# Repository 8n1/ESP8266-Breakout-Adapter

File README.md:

##ESP-07 & ESP-12 Breakout Adapter

###UPDATE [24.03.2016] - All Breakout Adapters are tested and working as expected. 
####Note: Documentations will be updated and completed within the next days.
<br />
####Version 1.1 - LM1117 (tested)
Used LDO: LM1117
Vin=4.8-15V, Dropout=1.2V, Iq=5mA

oshpark: https://oshpark.com/shared_projects/9CsYq2PY

####Version 2.0A - AS1363 (tested)
Used LDO: AS1363
Vin=3.5-5.5V, Dropout=150mV(-320mV), Iq=40µA

oshpark: https://oshpark.com/shared_projects/2IkxaFPm

####Version 2.0B - SPX3819 (tested)
Used LDO: SPX3819 
Vin=3.7-16V, Dropout=340mV(-550mV), Iq=90µA

oshpark: https://oshpark.com/shared_projects/jsl8ZcFp

####Version 3.1A - AS1363 - Mini (tested)
Used LDO: AS1363
Vin=3.5-5.5V, Dropout=150mV(-320mV), Iq=40µA

oshpark: https://oshpark.com/shared_projects/BgaX81QE

####Version 3.1B - SPX3819 - Mini (tested)
Used LDO: SPX3819 
Vin=3.7-16V, Dropout=340mV(-550mV), Iq=90µA

oshpark: https://oshpark.com/shared_projects/zpDg7761

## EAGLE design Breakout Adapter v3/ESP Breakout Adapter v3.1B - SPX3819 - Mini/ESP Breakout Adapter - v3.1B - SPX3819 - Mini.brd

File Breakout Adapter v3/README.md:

## V3 - Mini Adapter

### Changelog/Updates: <br />

V3.1 - Nov, 2015
- Footprint for VREG input and output capacitors changed from 1206 to 0805
- VREG bypass capacitor (C3) removed
- Bigger solderpads for the tactile switches
- Pullup resistor for GPIO2 added (R7)
- Part numbers on bottom side replaced with actual values
- Layout optimized
- Silkscreen fix (description of where the led is connected to was swapped: 3V3<->GPIO13)

V3.0 - Okt, 2015
- First version

### Pictures
V3.1B - OSH Park renderings<br />
&nbsp;

<br />
### Schematic

### Features
* ESP-07, ESP-12, ESP-12E and ESP-12F compatible (bottom header for E and F module is not brought out)
* On-board voltage regulator
* Flash and Reset switch
* Pullup resistors for Reset, CH_PD, GPIO0 and GPIO2
* Pulldown resistor for GPIO15
* On/Off Switch *
* LDO Enable Pin brougth out **
* DeepSleep wake-up jumper - Connects Pin8 and Pin32 and allows automatic deep-sleep wake-up
* On-board LED - Anode(+) can either be connected to the LDO ouptut ("3V3") or to "GPIO13" (selected using solderjumper)
* 2 Mountingholes (2.0mm)*)
* Expect for the headers fully SMD
* Breadboard compatible -> 3 rows stay free
* Very small

\* Can be used to completly shutdown the board and everything connected to it. The current consumption in this state will typically be &lt;1µA.  
\** Can be used to externaly turn the board on if the On/Off switch is set to "Off", or off if the On/Off switch is set to "On".

### Partlist (v3.1)
| Part  | Value                     | Info                |
|:------|:--------------------------|:--------------------|
| IC1   | AS1363-BSTT-33 (SOT23-6)  | Voltage regulator - Variant "A" |
| IC1   | SPX3819M5-L-3-3 (SOT23-5) | Voltage regulator - Variant "B" |
| C1    | 10µF (Ceramic, 0805)      | Input capacitor for the voltage regulator |
| C2    | 10µF (Ceramic, 0805)      | Output capacitor for the voltage regulator |
| C3    | 100nF (Ceramic, 0805)     | Decoupling capacitor for the ESP module |
| R1    | 10K (0805) *              | Pullup resistor for CH_PD |
| R2    | 10K (0805) *              | Pulldown resistor for GPIO15 |
| R3    | 10K (0805)                | Pullup resistor for Reset |
| R4    | 10K (0805)                | Pullup resistor for GPIO0 |
| R7    | 10K (0805)                | Pullup resistor for GPIO2 |
| R5    | 10K (0805)                | Pullup for LDO enable pin |
| R6    | 10K (0805)                | Pulldown for LDO enable pin |
| RV    | ~220 Ohm (0805)           | [Optional] Current limiting resistor for the led ** |
| LED   | LED (0805) **             | [Optional] Led of choice |
| DS    | Solderbridge       | DeepSleep wake-up jumper |
| FLASH | Tactile Pushbutton SMD 2pin 6x3       | Flash button |
| RESET | Tactile Pushbutton SMD 2pin 6x3       | Reset button |
| On/Off | SMD slide switch (DK: CKN10374CT-ND) (<a href="http://www.ebay.at/itm/20PCS-Mini-Slide-Power-Off-On-Panel-PCB-MINI-SMD-Solder-Switch-SPM-/120731615109">ebay</a>)       | On/Off switch |

\* **or** 0Ohm resistor/solderbridge if pin is not needed<br /> 
\** if the led is connected to GPIO13 the led current must be lower then 12mA, calculate the resister value accordingly!

Note:  
Pullup and Pulldown resistors(**R1, R2, R3, R4, R7**)  can range from 4.7K to 10K.  
Pullup and Pulldown resistor for the LDO enable pin(**R5, R6**) should be 10K or higher (100K max).  
Input and output capacitors for the voltage regualtor(**C1, C2**) are LOW ESR ceramic types. (I'm using: SAMSUNG CL21A106KOQNNNG)  

Pinheader
* 2x 1x10 (2.54mm)

Optional "socket" header for the esp module
* 2x 1x8 (2mm) female and male pin header

### Difference between variant A and B
The only difference is the used LDO. Variant A uses the AS1363, variant B the SPX3819(or pincompatible).

#### Resources:
- AS1363 Datasheet - https://ams.com/eng/content/download/1961/15107/file/AS1364_Datasheet_EN_v3.pdf
- SPX3819 Datasheet - https://www.adafruit.com/datasheets/SPX3819_DS_R202_052014.pdf

- More Pictures V3.1 - http://imgur.com/a/jSkG7 (imgur album)
- More Pictures V3.0 - http://imgur.com/a/w46x3 (imgur album)

#### This adapter on OSH Park:
- ESP8266 Breakout v3.1A - https://oshpark.com/shared_projects/RfAN6raq
- ESP8266 Breakout v3.1B - https://oshpark.com/shared_projects/OPku1n9U

#### License
<br />
Creative Commons Attribution 4.0 International<br />
http://creativecommons.org/licenses/by/4.0/

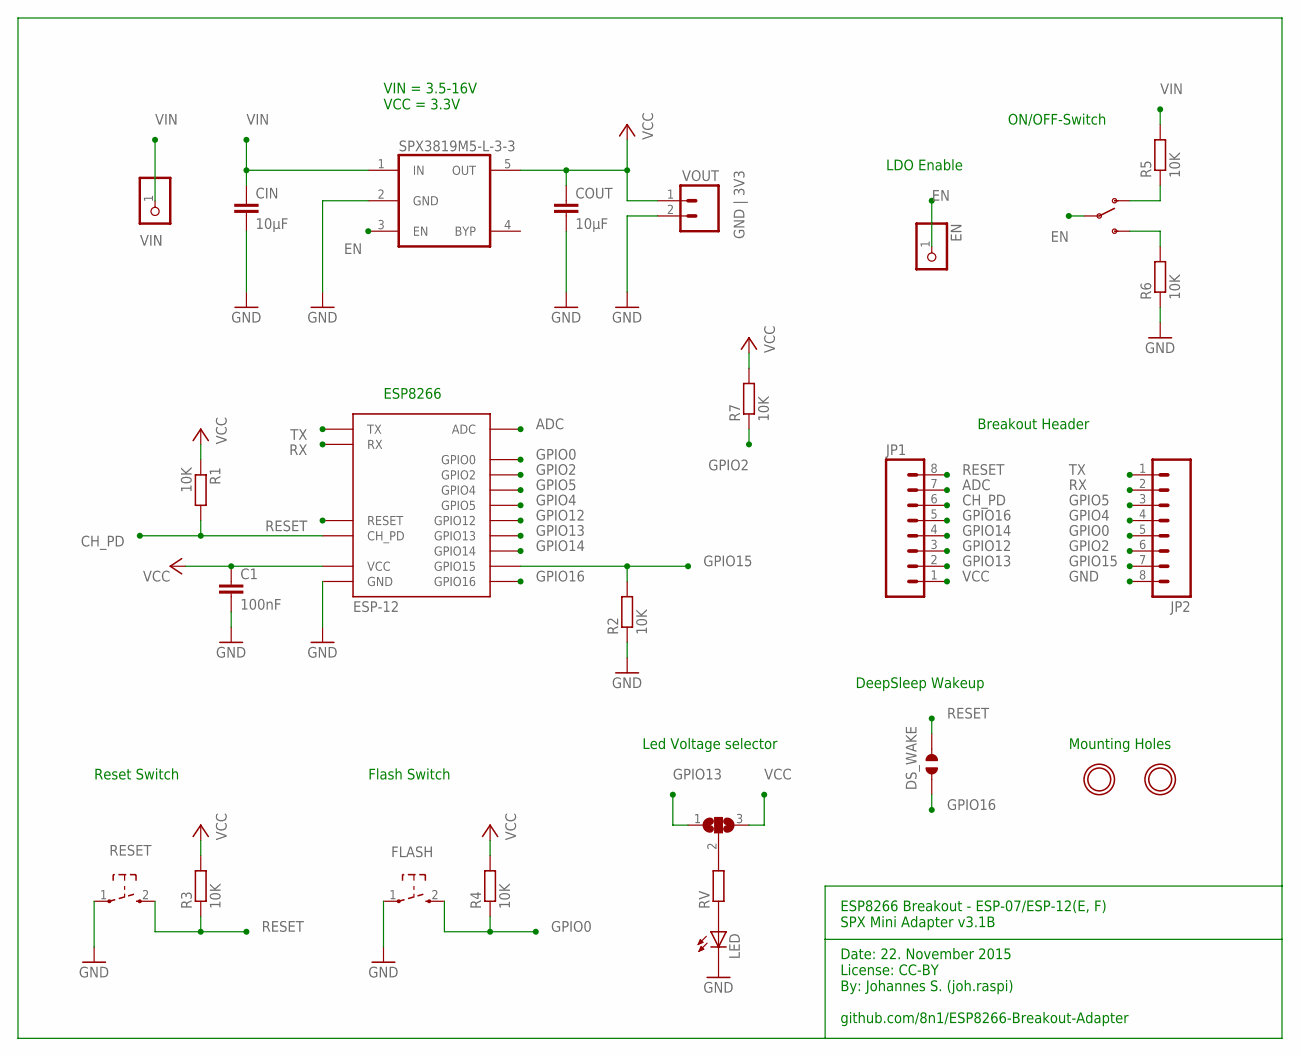
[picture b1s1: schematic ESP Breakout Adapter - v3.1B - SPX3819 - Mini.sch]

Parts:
C1: 100nF; C0805
CIN: 10µF; C0805
COUT: 10µF; C0805
DS_WAKE: JUMPER_SOLDER_1X2
EN: PINHD-1X1; 1X01
FLASH: SW_TACT_2P-3X6; SW_TACT_3X6
JP1, JP2: M081X08; 1X08
LED: LEDCHIPLED_0805; CHIPLED_0805
LED_VOLTAGE: SJ2W; SJ_2
ON/OFF-SWITCH: SWITCH_SPDT; KPS-1290
R1, R2, R3, R4, R5, R6, R7: 10K; R0805
RESET: SW_TACT_2P-3X6; SW_TACT_3X6
RV: R-EU_R0805; R0805
SPX3819M5-L-3-3: VREG_5PINS-SOT-23-5; SOT-23-5
U$1: ESP-12
U$4, U$5: MOUNTINGHOLE2.0; MOUNTINGHOLE_2.0_PLATED
VIN: M01PTH_2MM; 1X01-CLEANBIG
VOUT: GND | 3V3; 1X02

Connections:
123: ON/OFF-SWITCH.S, R6.2
ADC: JP1.7, U$1.ADC
CH_PD: JP1.6, R1.2, U$1.CH_PD
EN: EN.1, ON/OFF-SWITCH.P, SPX3819M5-L-3-3.3 (EN)
GND: C1.2, CIN.2, COUT.2, FLASH.1, JP2.8, LED.C, R2.1, R6.1, RESET.1, SPX3819M5-L-3-3.2 (GND), U$1.GND, VOUT.2
GPIO0: FLASH.2 (3), JP2.5, R4.1, U$1.GPIO0
GPIO2: JP2.6, R7.1, U$1.GPIO2
GPIO4: JP2.4, U$1.GPIO5
GPIO5: JP2.3, U$1.GPIO4
GPIO12: JP1.3, U$1.GPIO12
GPIO13: JP1.2, LED_VOLTAGE.1, U$1.GPIO13
GPIO14: JP1.4, U$1.GPIO14
GPIO15: JP2.7, R2.2, U$1.GPIO15
GPIO16: DS_WAKE.1, JP1.5, U$1.GPIO16
unnamed: LED_VOLTAGE.2, RV.2
unnamed: ON/OFF-SWITCH.O, R5.1
unnamed: LED.A, RV.1
RESET: DS_WAKE.2, JP1.8, R3.1, RESET.2 (3), U$1.RESET
RX: JP2.2, U$1.RX
TX: JP2.1, U$1.TX
VCC: C1.1, COUT.1, JP1.1, LED_VOLTAGE.3, R1.1, R3.2, R4.2, R7.2, SPX3819M5-L-3-3.5 (OUT), U$1.VCC, VOUT.1
VIN: CIN.1, R5.2, SPX3819M5-L-3-3.1 (IN), VIN.1

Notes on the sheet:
ESP8266 Breakout - ESP-07/ESP-12(E, F) SPX Mini Adapter v3.1B Date: 22. November 2015 License: CC-BY By: Johannes S. (joh.raspi) github.com/8n1/ESP8266-Breakout-Adapter
Mounting Holes
DeepSleep Wakeup
Breakout Header
VIN = 3.5-16V VCC = 3.3V
Led Voltage selector
LDO Enable
ON/OFF-Switch
Flash Switch
Reset Switch
ESP8266

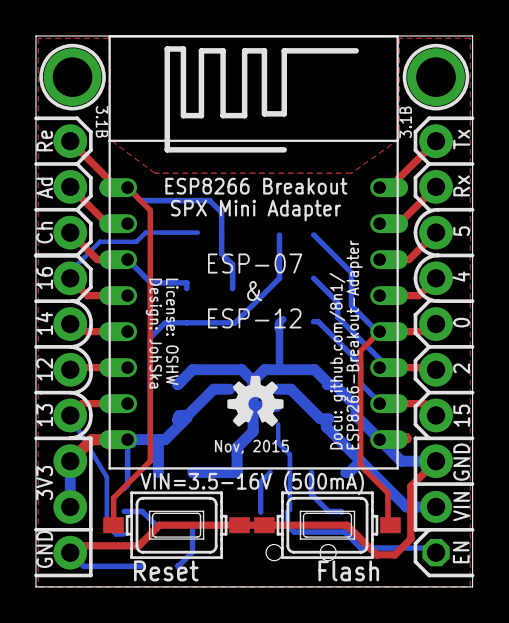
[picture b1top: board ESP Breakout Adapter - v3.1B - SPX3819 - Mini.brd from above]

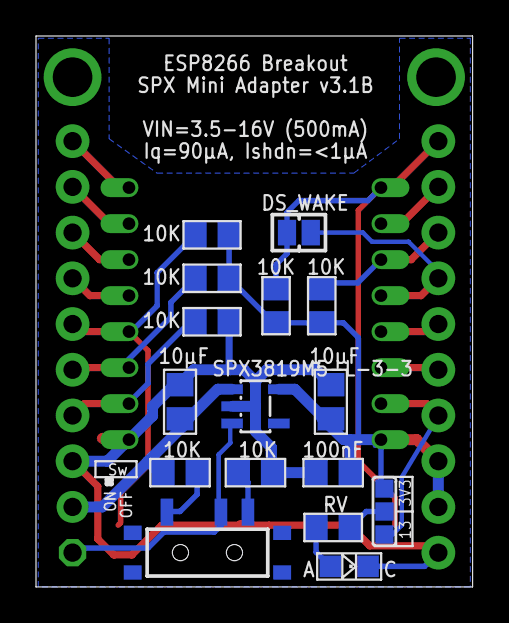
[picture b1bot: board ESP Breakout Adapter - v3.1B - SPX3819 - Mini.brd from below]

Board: 2 copper layers, 24.3 x 30.6 mm, 27 parts (16 on the bottom side), 22 nets.

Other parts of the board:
U$2: OSHW-LOGO-S

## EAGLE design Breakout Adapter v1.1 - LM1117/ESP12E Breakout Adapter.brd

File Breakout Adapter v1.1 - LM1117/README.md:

## V1 - 1117 Adapter
<br />

### Changelog/Updates: <br />
V1.1 - Aug, 2015
- Silkscreen optimizations
- Bottom silkscreen moved from layer bNames to bPlace
- Added lables for bottom header
- Smaller gnd vias (0.02755906)

V1.0 - Jun, 2015
- First version

### Pictures
V1.0 - Bare PCB<br />

<br />
V1.1 - OSH Park renderings<br />
&nbsp;

<br />
#### Schematic

### Features
* LM1117 Voltage regulator (or pin compatible)
* Flash und Reset switch
* Pullup resistors for Reset, CH_PD and GPIO0
* Pulldown resistor for GPIO15
* ESP-12E bottom header brougth out (see note)
* Breadboard compatible -> One row on both sides stays free
* Except for the headers and switches, fully SMD

##### Note: The additional bottom header on the ESP-12E can not be used without modifying the ESP module:
http://www.esp8266.com/viewtopic.php?f=32&t=4094

### Partlist (v1.1)
| Part  | Value                      | Info                |
|:------|:---------------------------|:--------------------|
| IC1   | LM1117 or pincompatible    | Voltage regulator |
| C1    | 10µF (Tantalum, Case B)      | Input capacitor for IC1 (see the Datasheet)|
| C2    | 10µF (Tantalum, Case B)      | Output capacitor for IC1 (see the Datasheet)|
| C3    | 100nF (Ceramic, 0805)      | Decoupling capacitor for the ESP module |
| R1    | 10K (0805) *               | Pullup resistor for CH_PD |
| R2    | 10K (0805) *               | Pulldown resistor for GPIO15 |
| R3    | 10K (0805)                 | Pullup resistor for Reset |
| R4    | 10K (0805)                 | Pullup resistor for GPIO0 |
| SW1   | Tactile switch (4pin,6x6,THT)       | Flash switch |
| SW2   | Tactile switch (4pin,6x6,THT)       | Reset switch |

\* **or** 0Ohm resistor/solderbridge if pin is not needed

Note:  
Pullup and Pulldown resistors(R1, R2, R3, R4) should range from 4.7K to 10K.  
Output capacitor for the voltage regualtor(C2) should be a tantalum type. (See the datasheet)

Pinheader
* 2x 1x8 (2.54mm)
* 2x 1x2 (2.54mm)
* (1x 1x6  (2.54mm)) - "E header"
<br />
Optional "socket" for the esp module
* 2x 1x8 (2mm)
* (1x 1x6 (2mm)) - "E header"

#### Resources:
- LM1117 Datasheet - http://www.ti.com/lit/ds/symlink/lm1117-n.pdf
- AMS1117 Datasheet - http://www.advanced-monolithic.com/pdf/ds1117.pdf

- More Pictures - http://imgur.com/a/fsVE8 (imgur album)

#### This adapter on OSH Park:
- ESP8266 Breakout v1.1 - https://oshpark.com/shared_projects/9CsYq2PY

#### License
<br />
Creative Commons Attribution 4.0 International<br />
http://creativecommons.org/licenses/by/4.0/

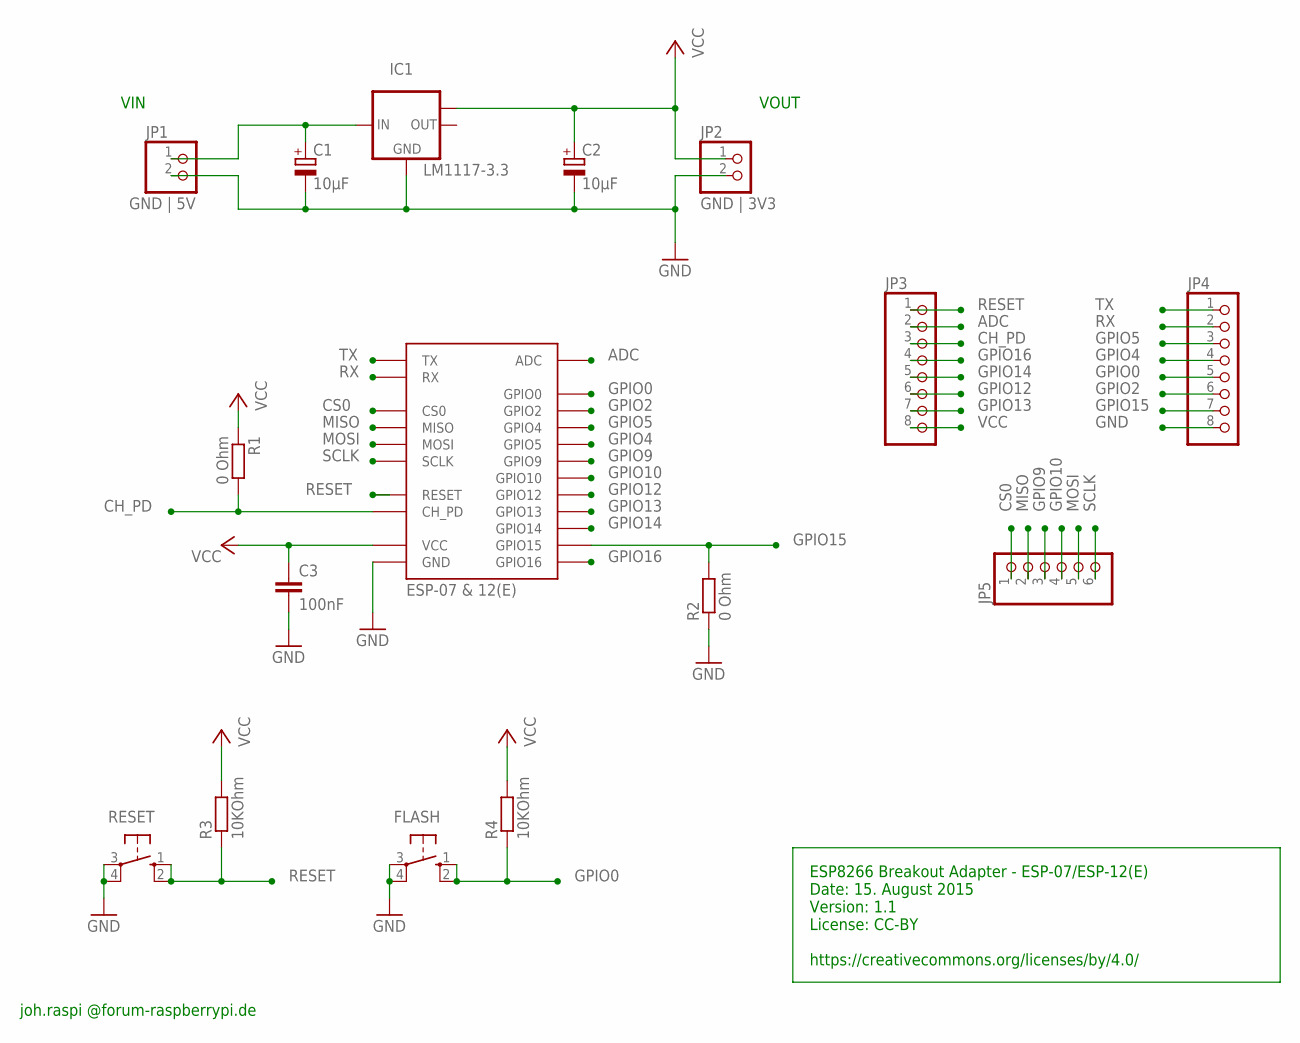
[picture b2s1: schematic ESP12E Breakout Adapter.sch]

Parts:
C1, C2: 10µF; B/3528-21W
C3: 100nF; C0805K
ESP8266: ESP-07 & 12(E); ESP-12-E
FLASH_SWITCH: FLASH; B3F-10XX
IC1: LM1117-3.3; SOT223
JP1: GND | 5V; 1X02
JP2: GND | 3V3; 1X02
JP3, JP4: PINHD-1X8; 1X08
JP5: PINHD-1X6; 1X06
R1, R2: 0 Ohm; R0805
R3, R4: 10KOhm; R0805
RESET_SWITCH: RESET; B3F-10XX

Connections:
ADC: ESP8266.ADC, JP3.2
CH_PD: ESP8266.CH_PD, JP3.3, R1.2
CS0: ESP8266.CS0, JP5.1
GND: C1.-, C2.-, C3.2, ESP8266.GND, FLASH_SWITCH.3, FLASH_SWITCH.4 (P1), IC1.1 (GND), JP1.2, JP2.2, JP4.8, R2.1, RESET_SWITCH.3, RESET_SWITCH.4 (P1)
GPIO0: ESP8266.GPIO0, FLASH_SWITCH.1 (S), FLASH_SWITCH.2 (S1), JP4.5, R4.1
GPIO2: ESP8266.GPIO2, JP4.6
GPIO4: ESP8266.GPIO5, JP4.4
GPIO5: ESP8266.GPIO4, JP4.3
GPIO9: ESP8266.GPIO9, JP5.3
GPIO10: ESP8266.GPIO10, JP5.4
GPIO12: ESP8266.GPIO12, JP3.6
GPIO13: ESP8266.GPIO13, JP3.7
GPIO14: ESP8266.GPIO14, JP3.5
GPIO15: ESP8266.GPIO15, JP4.7, R2.2
GPIO16: ESP8266.GPIO16, JP3.4
MISO: ESP8266.MISO, JP5.2
MOSI: ESP8266.MOSI, JP5.5
RESET: ESP8266.RESET, JP3.1, R3.1, RESET_SWITCH.1 (S), RESET_SWITCH.2 (S1)
RX: ESP8266.RX, JP4.2
SCLK: ESP8266.SCLK, JP5.6
TX: ESP8266.TX, JP4.1
VCC: C2.+, C3.1, ESP8266.VCC, IC1.TAB (OUT1), JP2.1, JP3.8, R1.1, R3.2, R4.2
VIN: C1.+, IC1.3 (IN), JP1.1

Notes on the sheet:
VIN
VOUT
ESP8266 Breakout Adapter - ESP-07/ESP-12(E) Date: 15. August 2015 Version: 1.1 License: CC-BY https://creativecommons.org/licenses/by/4.0/
joh.raspi @forum-raspberrypi.de

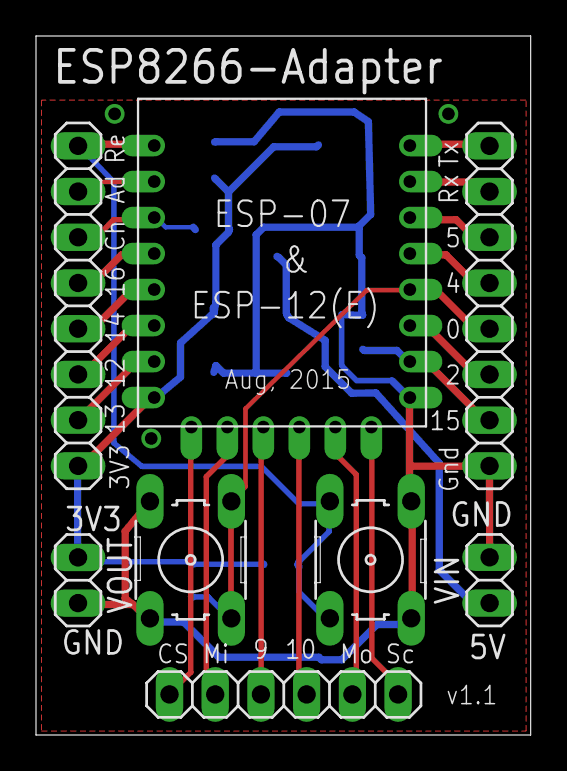
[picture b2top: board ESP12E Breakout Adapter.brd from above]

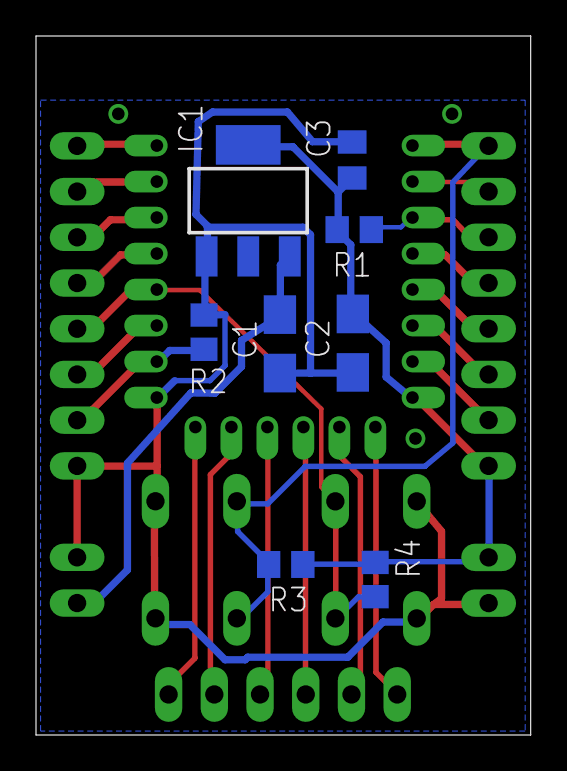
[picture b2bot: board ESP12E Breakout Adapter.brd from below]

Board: 2 copper layers, 27.5 x 38.8 mm, 16 parts (8 on the bottom side), 23 nets.

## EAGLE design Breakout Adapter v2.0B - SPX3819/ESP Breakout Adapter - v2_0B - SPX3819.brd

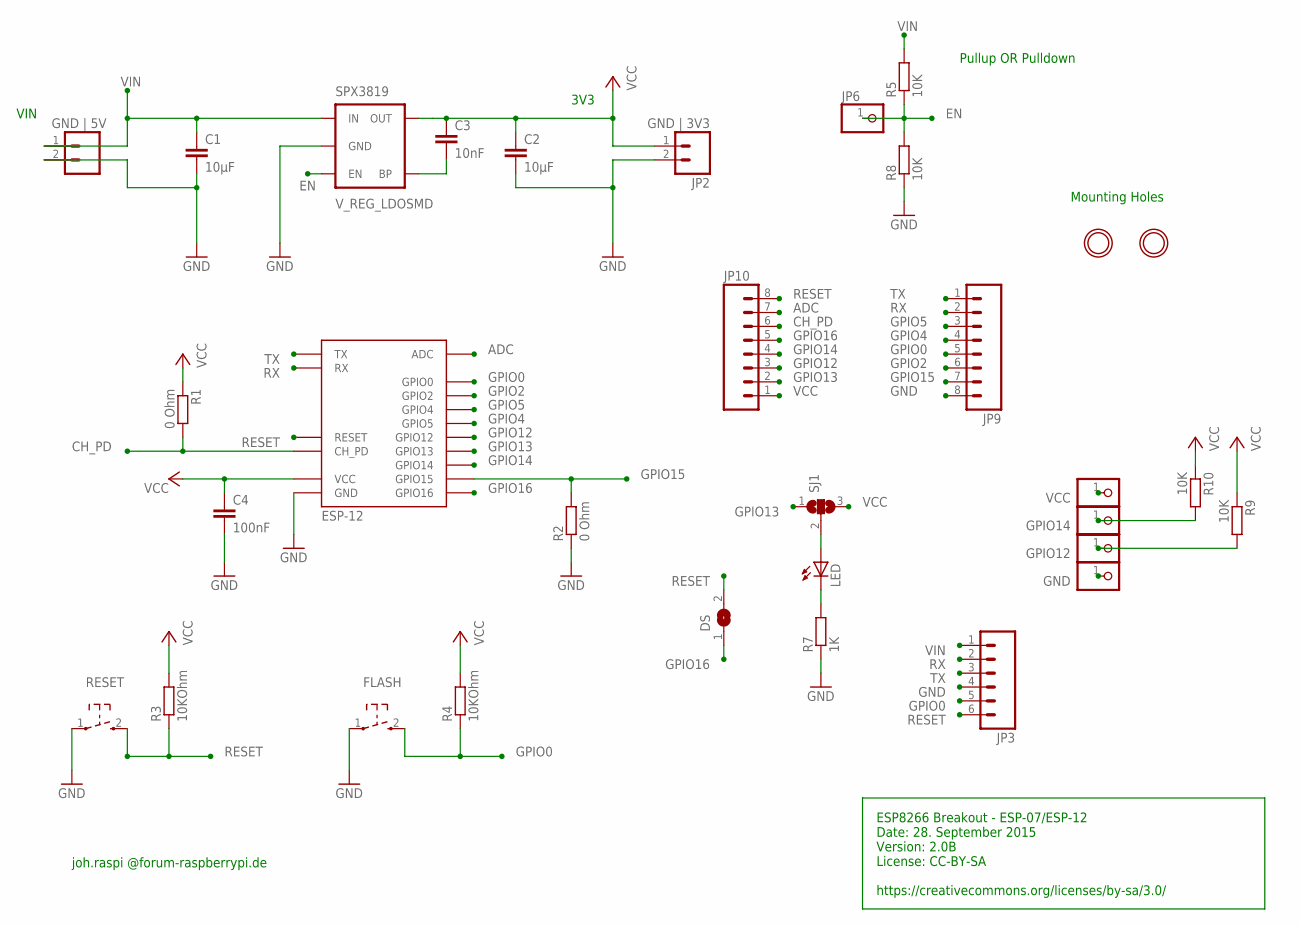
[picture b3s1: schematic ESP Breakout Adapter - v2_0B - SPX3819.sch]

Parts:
C1, C2: 10µF; C1206
C3: 10nF; C0603K
C4: 100nF; C0805
DS: SJ
FLASH: SW_TACT_2P-3X6; SW_TACT_3X6
JP1: GND | 5V; 1X02
JP2: GND | 3V3; 1X02
JP3: M06SIP; 1X06
JP4, JP6, JP7, JP8, JP11: PINHD-1X1; 1X01
JP9, JP10: M081X08; 1X08
LED: LED-0805; LED-805
R1, R2: 0 Ohm; R0805
R3, R4: 10KOhm; R0805
R5, R8, R9, R10: 10K; R0805
R7: 1K; R0805
RESET: SW_TACT_2P-3X6; SW_TACT_3X6
SJ1: SJ2W; SJ_2
SPX3819: V_REG_LDOSMD; SOT23-5
U$1: ESP-12
U$4, U$5: MOUNTINGHOLE2.0; MOUNTINGHOLE_2.0_PLATED

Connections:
ADC: JP10.7, U$1.ADC
CH_PD: JP10.6, R1.2, U$1.CH_PD
EN: JP6.1, R5.1, R8.2, SPX3819.3 (EN)
GND: C1.2, C2.2, C4.2, FLASH.1, JP1.2, JP2.2, JP3.4, JP4.1, JP9.8, R2.1, R7.1, R8.1, RESET.1, SPX3819.2 (GND), U$1.GND
GPIO0: FLASH.2 (3), JP3.5, JP9.5, R4.1, U$1.GPIO0
GPIO2: JP9.6, U$1.GPIO2
GPIO4: JP9.4, U$1.GPIO5
GPIO5: JP9.3, U$1.GPIO4
GPIO12: JP7.1, JP10.3, R9.2, U$1.GPIO12
GPIO13: JP10.2, SJ1.1, U$1.GPIO13
GPIO14: JP10.4, JP11.1, R10.2, U$1.GPIO14
GPIO15: JP9.7, R2.2, U$1.GPIO15
GPIO16: DS.1, JP10.5, U$1.GPIO16
unnamed: LED.C, R7.2
unnamed: LED.A, SJ1.2
RESET: DS.2, JP3.6, JP10.8, R3.1, RESET.2 (3), U$1.RESET
RX: JP3.2, JP9.2, U$1.RX
SET/BYP: C3.2, SPX3819.4 (BP)
TX: JP3.3, JP9.1, U$1.TX
VCC: C2.1, C3.1, C4.1, JP2.1, JP8.1, JP10.1, R1.1, R3.2, R4.2, R9.1, R10.1, SJ1.3, SPX3819.5 (OUT), U$1.VCC
VIN: C1.1, JP1.1, JP3.1, R5.2, SPX3819.1 (IN)

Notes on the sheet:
VIN
3V3
ESP8266 Breakout - ESP-07/ESP-12 Date: 28. September 2015 Version: 2.0B License: CC-BY-SA https://creativecommons.org/licenses/by-sa/3.0/
joh.raspi @forum-raspberrypi.de
Mounting Holes
Pullup OR Pulldown

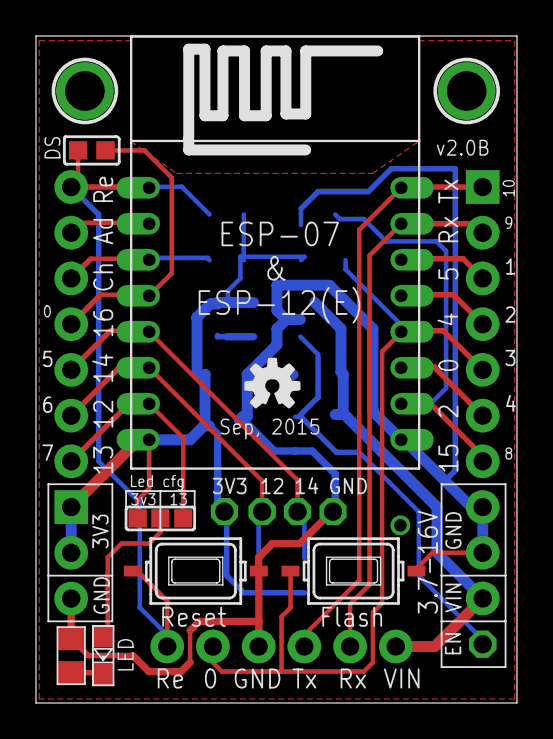
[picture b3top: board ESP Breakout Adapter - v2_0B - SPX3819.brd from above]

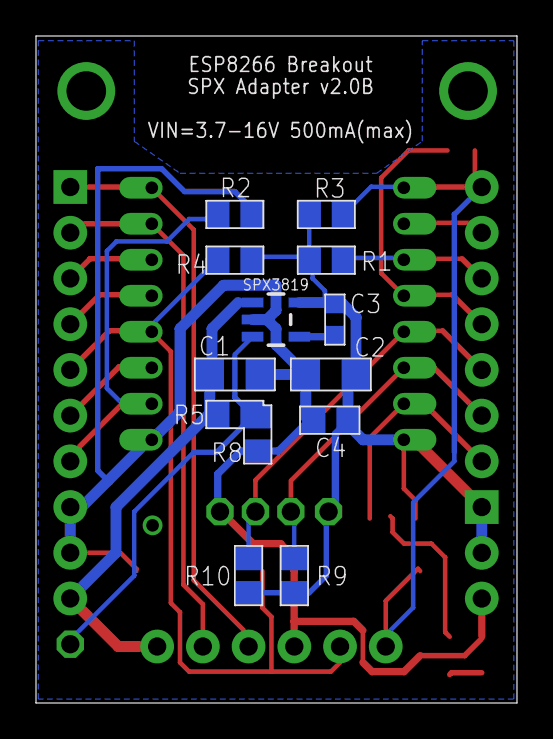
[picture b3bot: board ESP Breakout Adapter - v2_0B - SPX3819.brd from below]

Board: 2 copper layers, 26.7 x 37.1 mm, 33 parts (13 on the bottom side), 21 nets.

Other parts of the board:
U$3: OSHW-LOGO-S

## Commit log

2015-08-17 version 1.1
2015-08-17 weitere ergänzungen
2015-08-17 kleine ergänzung
2015-10-13 update version 2
2015-10-13 ergänzung
2015-10-13 kleine änderung
2015-10-16 mini adapter
2015-10-18 mini änderung
2015-10-18 neue versionierung
2016-03-24 updated documentation - adapters are tested....
2016-03-24 updated documentation
2016-04-14 updated docs, new version(3.1)
2016-04-20 added digikey slide switch part number add
2016-04-20 digikey slide switch part number added
2016-11-30 fixed variant description in partlst

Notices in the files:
Breakout Adapter v3/ESP Breakout Adapter v3.1B - SPX3819 - Mini/ESP Breakout Adapter - v3.1B - SPX3819 - Mini.brd:
License: OSHW
parts and their libraries:
SparkFun: Licensing: CC v3.0 Share-Alike You are welcome to use this library for commercial purposes.
microbuilder: This work is placed in the public domain, and may be freely used for commercial and non-commercial work with the following conditions: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
